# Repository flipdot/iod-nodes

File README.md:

# iod-nodes

ESP8266 based MQTT nodes controlled by Attiny.

This project covers battery powered WiFi devices running MQTT. The design goal was extremely low standby current for very long battery life.

The Attiny 25 in deep sleep consumes 120 nA. An interrupt on port change (mechanical switch) starts the Attiny which then switches on the Vcc of the ESP8266 via an MOSFET. After successfully connecting the WiFi and the MQTT broker and transmitting the current status the ESP8266 is shut down and the Attiny goes back into deep sleep.
The circuit supports supply by three Eneloop accumulators as well as by two alkaline primary cells.

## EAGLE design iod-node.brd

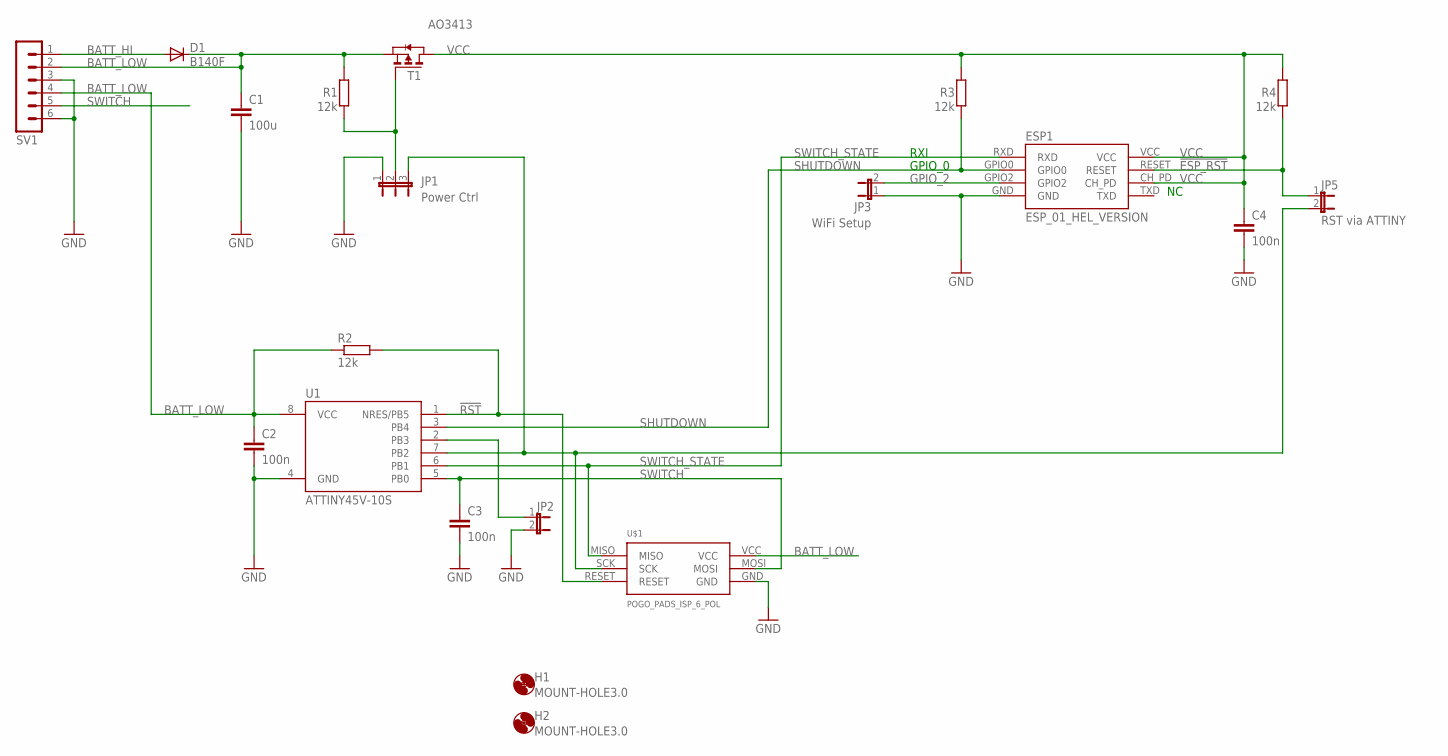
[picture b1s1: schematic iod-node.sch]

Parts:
C1: 100u; C1210
C2, C3, C4: 100n; C3225
D1: B140F; DO214AA
ESP1: ESP_01_HEL_VERSION; CUSTOM_ESP01_FOR_HEL
H1, H2: MOUNT-HOLE3.0; 3,0
JP1: Power Ctrl; JP2
JP2: JP1E; JP1
JP3: WiFi Setup; JP1
JP5: RST via ATTINY; JP1
R1, R2, R3, R4: 12k; R0805
SV1: MA06-1
T1: AO3413; SOT-23
U1: ATTINY45V-10S; SOIC8_EIAJ_208MIL
U$1: POGO_PADS_ISP_6_POL

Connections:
!ESP_RST: ESP1.RESET, JP5.1, R4.1
!RST: R2.2, U1.1 (NRES/PB5), U$1.RESET
BATT_HI: D1.A, SV1.1
BATT_LOW: C1.1, C2.1, D1.C, R1.2, R2.1, SV1.2, SV1.4, T1.2 (S), U1.8 (VCC), U$1.VCC
GND: C1.2, C2.2, C3.2, C4.2, ESP1.GND, JP1.1, JP2.2, JP3.1, SV1.3, SV1.6, U1.4 (GND), U$1.GND
GPIO_2: ESP1.GPIO2, JP3.2
unnamed: JP2.1, U1.2 (PB3)
unnamed: JP1.2, R1.1, T1.3 (G)
unnamed: JP1.3, JP5.2, U1.7 (PB2), U$1.SCK
SHUTDOWN: ESP1.GPIO0, R3.1, U1.3 (PB4)
SWITCH: C3.1, SV1.5, U1.5 (PB0), U$1.MOSI
SWITCH_STATE: ESP1.RXD, U1.6 (PB1), U$1.MISO
VCC: C4.1, ESP1.CH_PD, ESP1.VCC, R3.2, R4.2, T1.1 (D)

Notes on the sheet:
RXI
GPIO_0

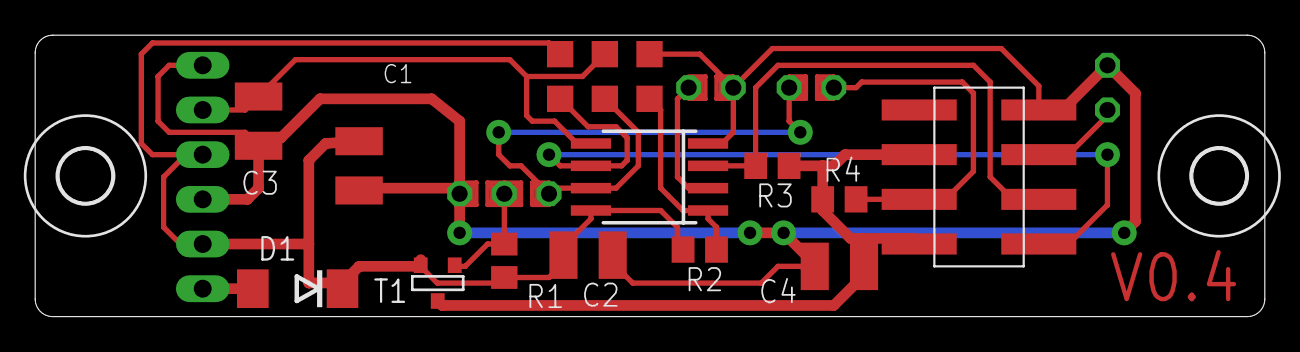
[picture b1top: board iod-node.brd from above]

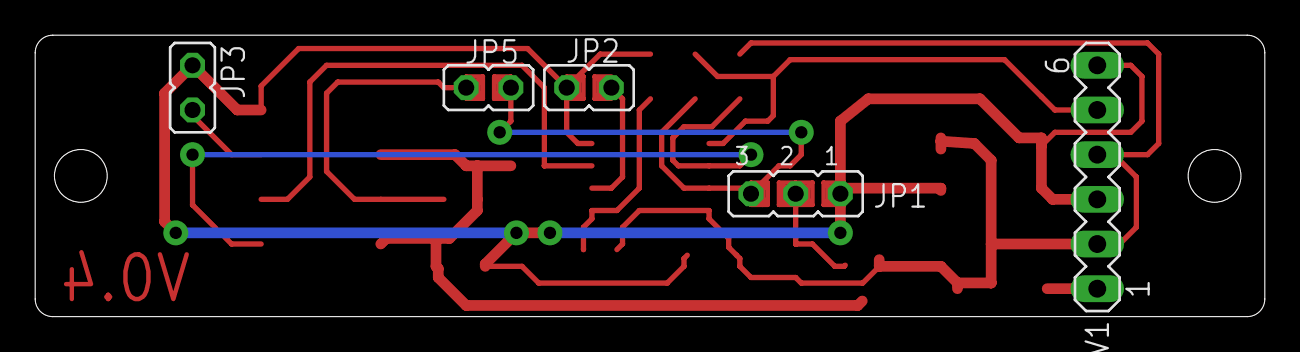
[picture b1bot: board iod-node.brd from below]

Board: 2 copper layers, 69.9 x 16.0 mm, 20 parts (5 on the bottom side), 13 nets.

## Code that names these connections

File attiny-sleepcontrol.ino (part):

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  +
  +  Pinout:
  +                   +-------------+
  +                 +-+ (PB5)   VCC +-+  BATT_LOW (Batteriespannung ueber Schottkyy-Diode)
  +                   | (Reset)     |
  +                   |             |
  +  DEBUG_LED      +-+ PB3     PB2 +-+  ESP_OFF (OUTPUT)
  +  (OUTPUT)         |             |
  +                   |             |
  +  SHUTDOWN       +-+ PB4     PB1 +-+  SWITCH_STATE (OUTPUT)
  +  (INPUT)          |             |
  +                   |             |
  +  GND            +-+ GND     PB0 +-+  SWITCH (INPUT)
  +                   +-------------+
  +
  +  Pin Funktionen:
  +  PB0 - SWITCH              - Umschalter, über den der ATtiny aus dem Tiefschlaf geweckt wird
  +  PB1 - SWITCH_STATE        - Der Zustand des Schalters wird für den ESP an diesem Pin ausgegeben
  +  PB2 - ESP_OFF             - Gate des MOSFET, High = ESP off, LOW = ESP on
  +  PB4 - SHUTDOWN            - Ein kurzes HIGH Signal an diesem Pin (vom ESP an den Tiny) bewirkt Abschalten des ESP und Sleep des Tiny
  +
  +  Ablauf:
  +  1. -> Der ATtiny wird durch einen PinChange(PC) Interrupt (Wechsel sowohl von HIGH nach LOW als auch umgekehrt möglich) am Pin PB0 geweckt.
  +  2. -> Der Tiny setzt PB2 auf LOW und aktiviert den MOSFET (und somit den ESP).
  +  3. -> Jetzt wird gewartet bis (vom ESP) ein Signal über PB4 kommt das den ATtiny veranlasst den ESP wieder abzuschalten,
         Ausserdem wird der Zustand des Schalters(PB0) immer wieder neu eingelesen und über PB1 ausgegeben.
  +  4. -> Ist nach "timerInterval" Sekunden noch kein Signal gekommen wird der ESP vom ATtiny wieder abgeschaltet -> PB2 geht auf HIGH
  +        Zusätzlich wird auch PB1 auf LOW gesetzt
  +  5. -> Zu guter letzt geht der ATtiny wieder in den Tiefschlaf(Power-down) und wartet auf den nächsten Interrupt.
  +        Der Stromverbrauch des ATtiny liegt während er schläft bei ca. ~300nA @3.8V. Im Datenblatt steht genauers.
  +
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
//------------------------------------------------------------------------------
// Pin Konfiguration
const int SWITCH = 0;               // PB.0
const int SWITCH_STATE = 1;         // PB.1
const int ESP_OFF = 2;              // PB.2
const int DEBUG_LED = 3;            // PB.3 
const int SHUTDOWN = 4;             // PB.4

// Anzahl Sekunden nach denen der ESP automatisch wieder abgeschaltet wird, wenn der ESP kein Abschaltsignal geliefert hat
const unsigned long timerInterval = 20;
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{
  // GPIOs konfigurieren
  pinMode(ESP_OFF, OUTPUT);
  pinMode(SHUTDOWN, INPUT);
  pinMode(SWITCH_STATE, OUTPUT);
  pinMode(SWITCH, INPUT);                                   // SWITCH input bekommen keinen pullup, da Wechselschalter angeschlossen wird. Pullup würde unnoetigen Strom ziehen
  pinMode(DEBUG_LED, OUTPUT);
  digitalWrite(DEBUG_LED, LOW);                             // Pullup Widerstand für den unbenutzen Pin: Floating vermeiden (Stromverbrauch!)

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{
  if (goto_sleep == true)                                   // Flag für schlafen gehen gesetzt?
  {
    digitalWrite(SWITCH_STATE, LOW);                        // SWITCH_STATE beim Schlafen auf LOW setzen, weil dieser Pin einen spannungslosen ESP
                                                            // treibt, bei HIGH => Spannung am IO-Port > Vcc, das ist nicht erlaubt
    digitalWrite(ESP_OFF, HIGH);                            // ESP abschalten

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    digitalWrite(ESP_OFF, LOW);                             // ESP einschalten
    start_time = millis();                                  // Startzeit einlesen    
    delay(100);                                             // Entprellen
    digitalWrite(SWITCH_STATE, digitalRead(SWITCH));        // Zustand des Schalters(PB0) auf PB1 für ESP ausgeben
    switch_state_old = digitalRead(SWITCH);                 // Schalterstellung beim Aufwecken merken        
    delay(400);                                             // Nötig, weil der Pullup am esp anfangs die shutdown Leitung noch auf HIGH zieht. (Schaltungs-Design-Fehler)
                                                            // wenn der ESP gestartet ist, dann zieht er shutdown auf LOW                                                    
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      start_time = millis();                                // Startzeit einlesen    
      digitalWrite(ESP_OFF, LOW);                           // ESP einschalten, und geänderte Schalterstellung übertragen
      delay(500);                                           // Nötig, weil der pullup am esp anfangs die shutdown leitung noch auf HIGH zieht. (Schaltungs-Design-Fehler)
      digitalWrite(SWITCH_STATE, digitalRead(SWITCH));      // Zustand des Schalters(PB0) auf PB1 ausgeben
      switch_state_old = digitalRead(SWITCH);               // Aktuelle Schalterstellung merken

    }
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
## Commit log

2017-10-10 publishes json-string
2017-10-13 add actuator-firmware
2017-10-21 Fix README.md formatting, add fuse settings image
